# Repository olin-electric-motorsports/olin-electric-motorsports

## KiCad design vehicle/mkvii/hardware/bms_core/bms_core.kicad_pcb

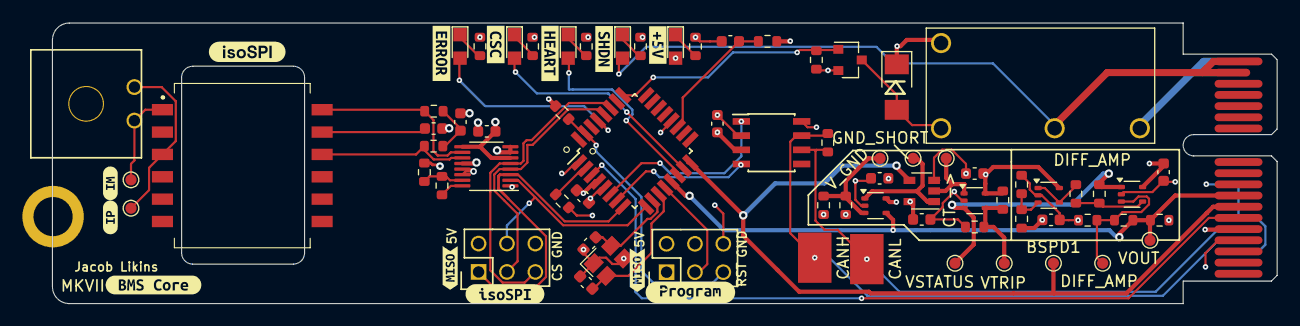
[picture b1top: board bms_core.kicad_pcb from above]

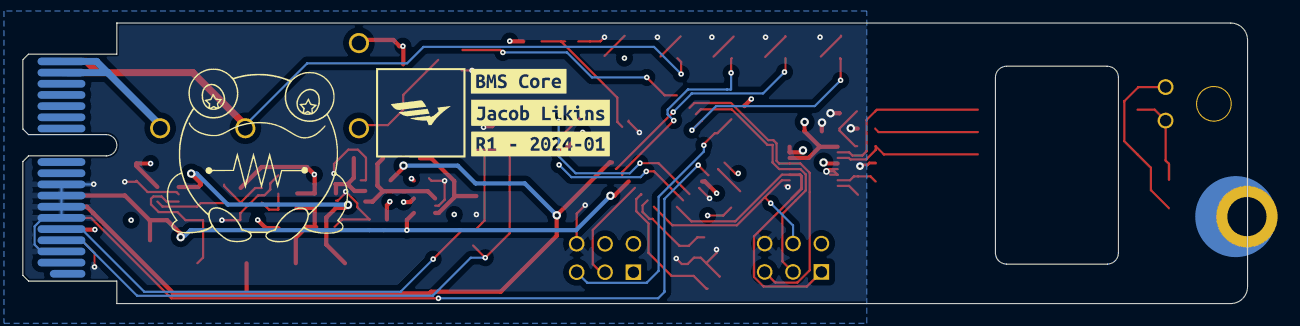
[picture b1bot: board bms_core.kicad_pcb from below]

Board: 4 copper layers, 109.6 x 25.1 mm, 89 parts (3 on the bottom side), 50 nets.

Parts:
BSPD1: BSPD_CURRENT_THRESH; TestPoint_Pad_D1.0mm
C1, C4, C6, C9, C10, C11, C12, C13: C_0.1uF; C_0603
C2: C_100pF; C_0603
C3, C5: C_30pF; C_0603
C7, C8: C_10nF; C_0603
CANH: CANH1; Test_Point_SMD
CANL: CANL1; Test_Point_SMD
CT ->: CURRENT_TRIP; TestPoint_Pad_D1.0mm
D1: LED_AMBER; CHIPLED_0805
D2: LED_GREEN; CHIPLED_0805
D3: LED_RED; CHIPLED_0805
D4: LED_WHITE; CHIPLED_0805
D5: D_Zener_18V_SMBJ5355B-TP; DO-214AA
D6: LED_BLUE; CHIPLED_0805
DIFF_AMP: TP_1mm; TestPoint_Pad_D1.0mm
GND_SHORT: GND_SHORT; TestPoint_Pad_D1.0mm
H2: CONN_MountingHole; PCIe_Mount
IM1: TP_1mm; TestPoint_Pad_D1.0mm
IP1: TP_1mm; TestPoint_Pad_D1.0mm
J1, J2: CONN_02x03; Pin_Header_Straight_2x03
J3: MicroFit_RA_2
J5: CONN_pcie_x1; pcie_x1
K1: Relay_G5Q-1A4-DC5; Relay_SPST_OMRON-G5Q-1A4_OEM
Q1: SSM3K333R; SOT-23F
R1, R3, R21, R22, R23: 1KR; R_0603
R2: R_100; R_0603
R4: 100R; R_0603
R5: R_120_DNP; R_0603
R6, R7, R12, R13, R14, R15, R16, R19, R24, R25: R_10K; R_0603
R8, R9, R18: R_1K; R_0603
R10, R11: R_60.4; R_0603
R17: R_1M; R_0603
R20: R_576; R_0603
T1: HM2112ZNLT
U1: ATMEGA64M1; TQFP-32_7x7mm_Pitch0.8mm
U2: MAX33011EASA; SOIC-8_3.9x4.9mm_Pitch1.27mm_OEM
U3: LTC6820HMS; MSOP-16_3x4mm_P0.5mm
U4, U5, U6, U8: MCP6001; SOT-353_SC-70-5
U7: SN74LVC1G32DBVR; SOT-23-5_OEM
VOUT: VOUT; TestPoint_Pad_D1.0mm
VSTATUS: VSTATUS; TestPoint_Pad_D1.0mm
VTRIP: VTRIP; TestPoint_Pad_D1.0mm
V_GND: V_GND_THRESHOLD; TestPoint_Pad_D1.0mm
Y1: Crystal_16MHz_18pF; Crystal_SMD_FA238
kibuzzard-63B930AD, kibuzzard-63B930AD#2: G***; kibuzzard-63B930AD
kibuzzard-63B9305B: G***; kibuzzard-63B9305B
kibuzzard-63B93076: G***; kibuzzard-63B93076
kibuzzard-63BB8A3F: G***; kibuzzard-63BB8A3F
kibuzzard-63BB8A53: G***; kibuzzard-63BB8A53
kibuzzard-63BF4A21: G***; kibuzzard-63BF4A21
kibuzzard-63BF57C4: G***; kibuzzard-63BF57C4
kibuzzard-673AE5B2: G***; kibuzzard-673AE5B2
kibuzzard-673AE5D1: G***; kibuzzard-673AE5D1
kibuzzard-673AE69E: G***; kibuzzard-673AE69E
kibuzzard-673AE93C: G***; kibuzzard-673AE93C
kibuzzard-673AE677: G***; kibuzzard-673AE677
kibuzzard-673AE688: G***; kibuzzard-673AE688
kibuzzard-673AE955: G***; kibuzzard-673AE955
kibuzzard-673AE966: G***; kibuzzard-673AE966

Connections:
+5V: C1.1, C4.1, C6.1, C9.1, C10.1, C11.1, C12.1, C13.1, D4.2 (A), D5.1 (K), J1.2, J2.2, J5.B5 (5V), K1.5, R2.1, R6.1, R12.2, R17.1, R19.2, R24.1, U1.4 (VCC), U2.3 (VDD), U3.6 (VDDS), U3.7 (POL), U3.8 (PHA), U3.9 (VDD), U3.12 (MSTR), U4.5 (V+), U5.5 (V+), U6.5 (V+), U7.5 (VCC), U8.5 (V+)
/BMS_RELAY_DRIVE: Q1.1 (G), R7.2, U1.25 ((PCINT15/D2A/AMP2+)PC7)
/BSPD Current Sensor Trigger/CURRENT_TRIP: CT ->.1, U6.1, U7.2 (in)
/BSPD Current Sensor Trigger/GND_SHORT: GND_SHORT.1, U5.1, U7.1 (in)
/BSPD Current Sensor Trigger/VSTATUS: R15.2, U4.1, U6.3 (+), VSTATUS.1
/BSPD Current Sensor Trigger/VTRIP: R19.1, R20.1, U6.4 (-), VTRIP.1
/BSPD Current Sensor Trigger/V_GND_THRESHOLD: R17.2, R18.1, U5.3 (+), V_GND.1
/BSPD_CURRENT_THRESH: BSPD1.1, J5.B7 (io_3), U1.16 ((PCINT2/ADC5/INT1/ACMPN0)PB2), U7.4 (out)
/CANH: CANH.1, J5.A4 (CAN+), R5.1, U2.7 (CANH)
/CANL: CANL.1, J5.A5 (CAN-), R5.2, U2.6 (CANL)
/CSC_Comms: D2.2 (A), U1.15 ((PCINT23/ACMP0)PD7)
/Error: D3.2 (A), U1.29 ((PCINT16/PSCOUT0A)PD0)
/FAN_PWM: J5.B6 (io_1), U1.3 ((PCINT9/PSCIN1/OC1B/~SS_A)PC1)
/Heartbeat: D1.2 (A), U1.14 ((PCINT22/ADC3/INT0/ACMPN2)PD6)
/IM: IM1.1, J3.1, T1.1
/IP: IP1.1, J3.2, T1.3
/ISO_CS: J2.5, U1.27 ((PCINT6/ADC7/PSCOUT1B)PB6), U3.5 (~CS)
/ISO_MISO: J2.1, U1.8 ((PCINT0/MISO/PSCOUT2A)PB0), U3.3 (MISO)
/ISO_MOSI: J2.4, U1.9 ((PCINT1/MOSI/PSCOUT2B)PB1), U3.2 (MOSI)
/ISO_SCK: J2.3, U1.28 ((PCINT7/ADC4/SCK/PSCOUT0B)PB7), U3.4 (SCK)
/MISO: J1.1, U1.1 ((PCINT18/PSCIN2/OC1A/MISO_A)PD2)
/MOSI: J1.4, R4.1
/RESET: J1.5, R6.2, U1.31 ((PCINT24/OCD/~RESET)PE0)
/RXCAN: U1.7 ((PCINT11/T1/ICP1B/RXCAN)PC3), U2.4 (RXD)
/SCK: J1.3, U1.12 ((PCINT20/ADC1/RXD/RXLIN/ICP1A/SCK_A)PD4)
/SHDN_IN: J5.A17 (SHDN_IN/io_22), J5.A18 (SHDN_IN/io_24), K1.3
/SHDN_OUT: D6.2 (A), J5.B17 (SHDN_OUT/io_23), J5.B18 (SHDN_OUT/io_25), K1.2
/TXCAN: U1.6 ((PCINT10/T0/TXCAN)PC2), U2.1 (TXD)
/VOUT_CURRENT_SENSE: J5.B8 (io_5), R12.1, R13.1, U1.13 ((PCINT21/ADC2/ACMP2)PD5), U5.4 (-), VOUT.1
GND: C1.2, C2.2, C3.2, C4.2, C5.2, C6.2, C7.2, C8.2, C9.2, C10.2, C11.2, C12.2, C13.2, J1.6, J2.6, J5.A3 (GND), J5.A6 (io_0), J5.A7 (io_2), J5.A8 (io_4), J5.A9 (io_6), J5.B4 (GND), Q1.2 (S), R1.2, R3.2, R7.1, R9.2, R14.1, R18.2, R20.2, R21.2, R22.2, R23.2, R25.2, U1.5 (GND), U1.20 (AGND), U2.2 (VSS), U2.8 (STBY), U3.1 (EN), U3.13 (SLOW), U3.14 (GND), U4.2 (V-), U5.2 (V-), U6.2 (V-), U7.3 (GND), U8.2 (V-), Y1.2, Y1.4
unnamed: C7.1, R10.2, R11.1
unnamed: C8.1, T1.11
unnamed: D1.1 (K), R1.1
unnamed: D2.1 (K), R3.1
unnamed: D3.1 (K), R21.1
unnamed: D4.1 (K), R22.1
unnamed: D5.2 (A), K1.1, Q1.3 (D)
unnamed: D6.1 (K), R23.1
unnamed: R4.2, U1.2 ((PCINT19/TXD/TXLIN/OC0A/~SS/MOSI_A)PD3)
unnamed: C5.1, U1.10 ((PCINT25/OC0B/XTAL1)PE1), Y1.3
unnamed: C3.1, U1.11 ((PCINT26/ADC0/XTAL2)PE2), Y1.1
unnamed: C2.1, R2.2, U1.19 (AVCC)
unnamed: R8.1, U3.16 (IBIAS)
unnamed: R8.2, R9.1, U3.15 (ICMP)
unnamed: R10.1, T1.12, U3.10 (IM)
unnamed: R11.2, T1.10, U3.11 (IP)
unnamed: DIFF_AMP.1, R13.2, R14.2, U4.3 (+)
unnamed: R15.1, R16.2, U4.4 (-)
unnamed: R24.2, R25.1, U8.3 (+)
unnamed: R16.1, U8.1, U8.4 (-)

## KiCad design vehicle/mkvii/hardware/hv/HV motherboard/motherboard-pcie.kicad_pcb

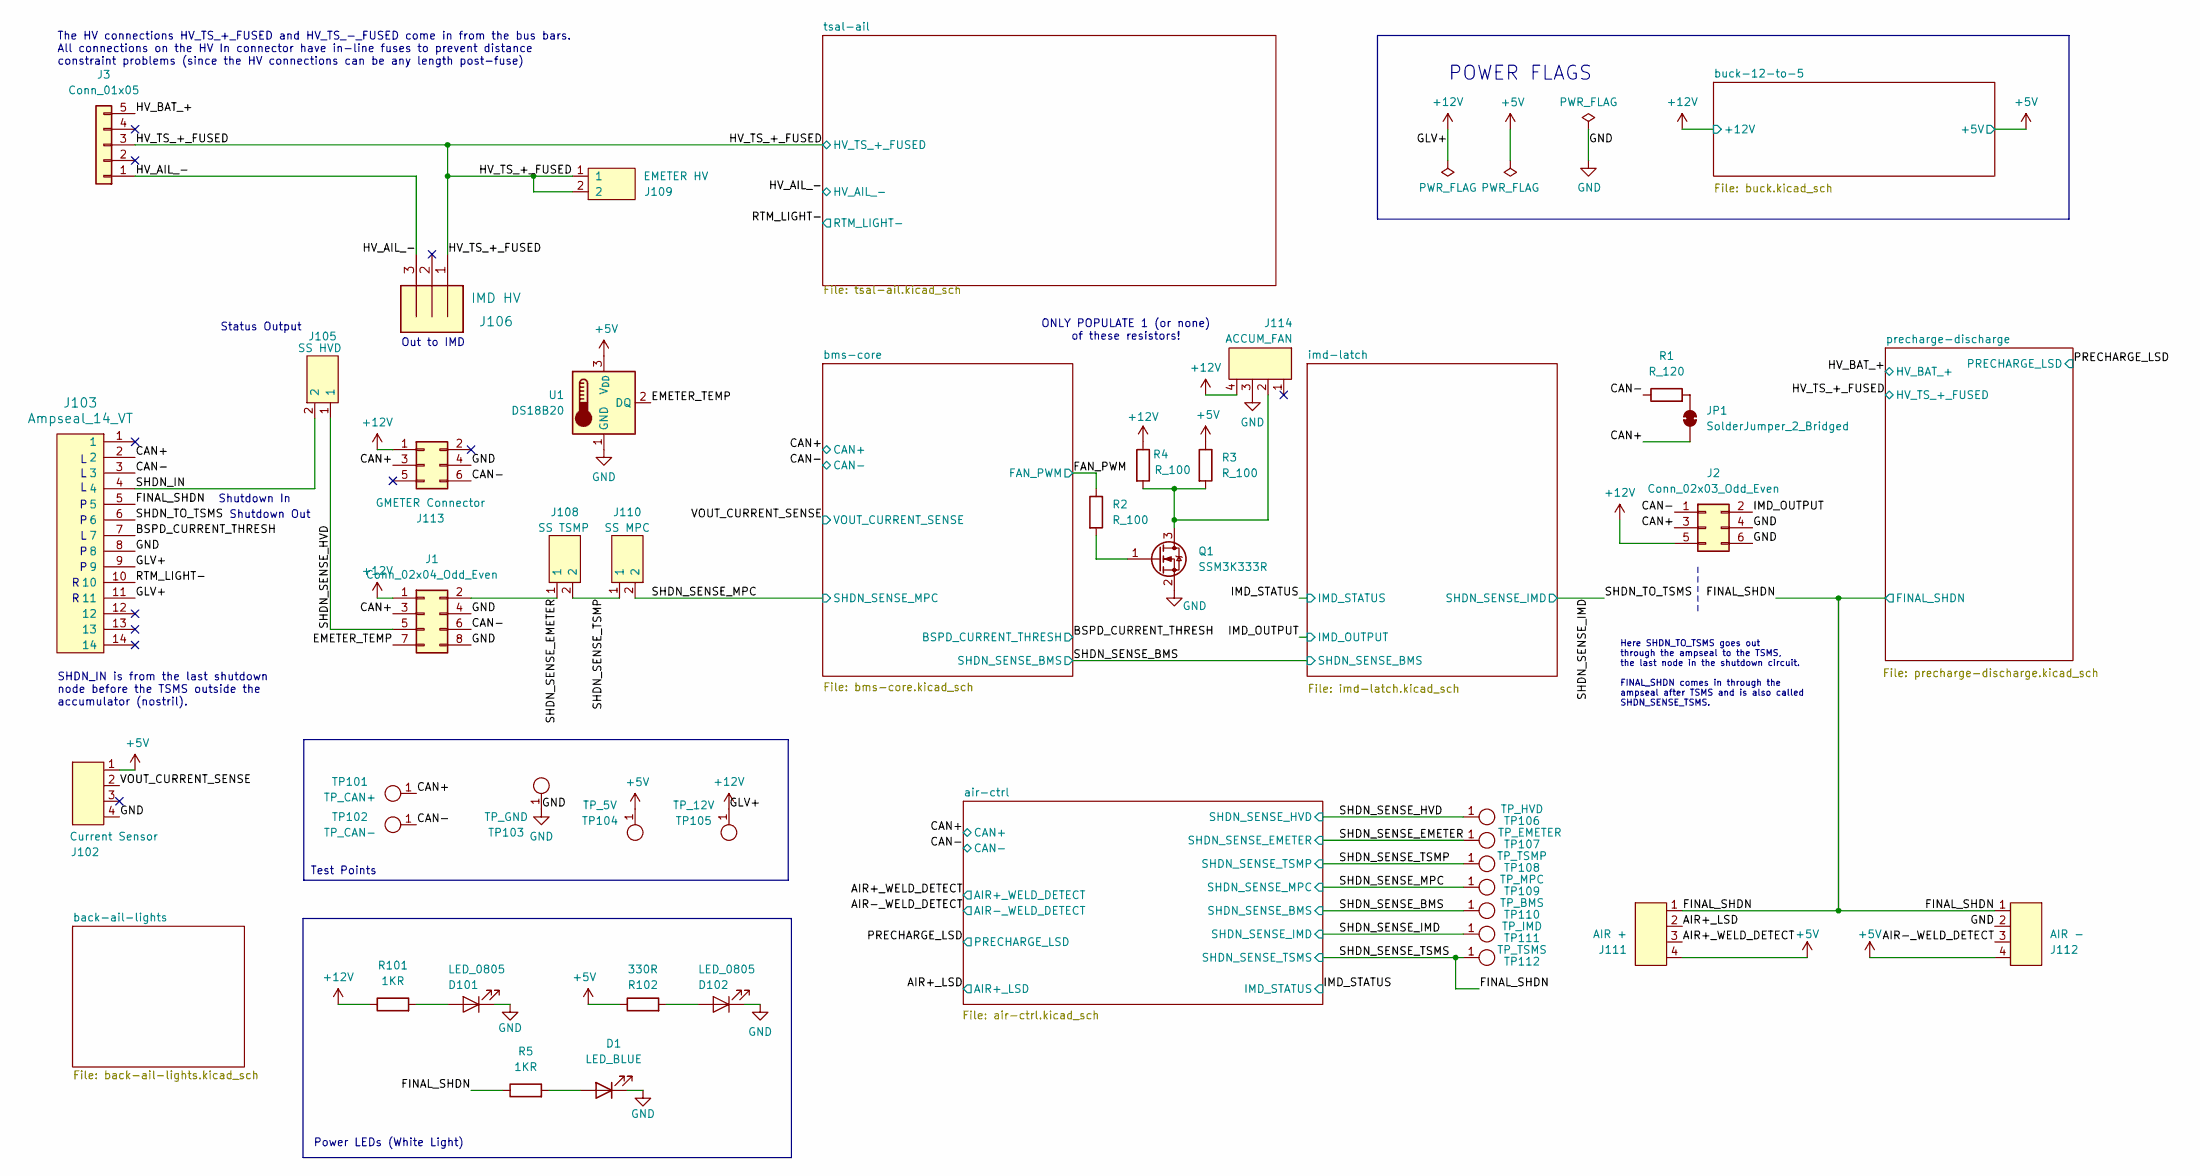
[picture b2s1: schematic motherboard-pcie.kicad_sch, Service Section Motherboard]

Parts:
D1: LED_BLUE; CHIPLED_0805; MPN LTST-C171TBKT
D101, D102: LED_0805; LED_0805_OEM; MPN 475-1410-1-ND
J1: Conn_02x04_Odd_Even; Molex_Micro-Fit_3.0_43045-0812_2x04_P3.00mm_Vertical
J2: Conn_02x03_Odd_Even; Molex_Micro-Fit_3.0_43045-0612_2x03_P3.00mm_Vertical
J3: Conn_01x05; Molex_Micro-Fit_3.0_43650-0515_1x05_P3.00mm_Vertical
J102: Current Sensor; MicroFit_VT_4; MPN 430450414
J103: Ampseal_14_VT; Ampseal_14; MPN 1-776261-1
J105: SS HVD; MicroFit_V_2; MPN WM10660-ND
J106: IMD HV; MicroFit_VT_3; MPN 436500327
J108: SS TSMP; MicroFit_V_2; MPN WM10660-ND
J109: EMETER HV; MicroFit_V_2; MPN WM10660-ND
J110: SS MPC; MicroFit_V_2; MPN WM10660-ND
J111: AIR +; MicroFit_VT_4; MPN 430450414
J112: AIR -; MicroFit_VT_4; MPN 430450414
J113: GMETER Connector; Molex_Micro-Fit_3.0_43045-0612_2x03_P3.00mm_Vertical
J114: ACCUM_FAN; MicroFit_VT_4; MPN 430450414
JP1: SolderJumper_2_Bridged; SolderJumper-2_P1.3mm_Bridged2Bar_Pad1.0x1.5mm
Q1: SSM3K333R; SOT-23F; MPN SSM3K333R,LF
R1: R_120; R_0603; MPN RC0603FR-13120RL
R2, R3, R4: R_100; R_0603; MPN RMCF0603FT1K00
R5, R101: 1KR; R_0603; MPN RMCF0603FT1K00
R102: 330R; R_0603; MPN WR06X3300FTL
TP101: TP_CAN+; Test_Point_SMD; MPN 5019
TP102: TP_CAN-; Test_Point_SMD; MPN 5019
TP103: TP_GND; Test_Point_SMD; MPN 5019
TP104: TP_5V; Test_Point_SMD; MPN 5019
TP105: TP_12V; Test_Point_SMD; MPN 5019
TP106: TP_HVD; Test_Point_SMD; MPN 5019
TP107: TP_EMETER; Test_Point_SMD; MPN 5019
TP108: TP_TSMP; Test_Point_SMD; MPN 5019
TP109: TP_MPC; Test_Point_SMD; MPN 5019
TP110: TP_BMS; Test_Point_SMD; MPN 5019
TP111: TP_IMD; Test_Point_SMD; MPN 5019
TP112: TP_TSMS; Test_Point_SMD; MPN 5019
U1: DS18B20; TO-92_Inline

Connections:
+5V: J102.1, J111.4, J112.4, R3.1, R102.1, TP104.1, U1.3 (V_{DD}); also elsewhere on the board
+12V: J1.1, J2.5, J103.9, J103.11, J113.1, J114.4, R4.1, R101.1, TP105.1; also elsewhere on the board
/AIR+_LSD: J111.2; also elsewhere on the board
/AIR+_WELD_DETECT: J111.3; also elsewhere on the board
/AIR-_WELD_DETECT: J112.3; also elsewhere on the board
/BSPD_CURRENT_THRESH: J103.7; also elsewhere on the board
/CAN+: J1.3, J2.3, J103.2, J113.3, JP1.1 (A), TP101.1; also elsewhere on the board
/CAN-: J1.6, J2.1, J103.3, J113.6, R1.1, TP102.1; also elsewhere on the board
/EMETER_TEMP: J1.7, U1.2 (DQ)
/FAN_PWM: R2.1; also elsewhere on the board
/FINAL_SHDN: J103.5, J111.1, J112.1, R5.1, TP112.1; also elsewhere on the board
/HV_AIL_-: J3.1, J106.3; also elsewhere on the board
/HV_BAT_+: J3.5; also elsewhere on the board
/HV_TS_+_FUSED: J3.3, J106.1, J109.1, J109.2; also elsewhere on the board
/IMD_OUTPUT: J2.2; also elsewhere on the board
/RTM_LIGHT-: J103.10; also elsewhere on the board
/SHDN_IN: J103.4, J105.2
/SHDN_SENSE_BMS: TP110.1; also elsewhere on the board
/SHDN_SENSE_EMETER: J1.2, J108.1, TP107.1; also elsewhere on the board
/SHDN_SENSE_HVD: J1.5, J105.1, TP106.1; also elsewhere on the board
/SHDN_SENSE_IMD: J103.6, TP111.1; also elsewhere on the board
/SHDN_SENSE_MPC: J110.2, TP109.1; also elsewhere on the board
/SHDN_SENSE_TSMP: J108.2, J110.1, TP108.1; also elsewhere on the board
/VOUT_CURRENT_SENSE: J102.2; also elsewhere on the board
GND: D1.1 (K), D101.1 (K), D102.1 (K), J1.4, J1.8, J2.4, J2.6, J102.4, J103.8, J112.2, J113.4, J114.3, Q1.2 (S), TP103.1, U1.1 (GND); also elsewhere on the board
unnamed: D1.2 (A), R5.2
unnamed: D101.2 (A), R101.2
unnamed: D102.2 (A), R102.2
unnamed: JP1.2 (B), R1.2
unnamed: J114.2, Q1.3 (D), R3.2, R4.2
unnamed: Q1.1 (G), R2.2

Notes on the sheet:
SHDN_IN is from the last shutdown node before the TSMS outside the accumulator (nostril).
Shutdown Out
Test Points
Shutdown In
Here SHDN_TO_TSMS goes out through the ampseal to the TSMS, the last node in the shutdown circuit. FINAL_SHDN comes in through the ampseal after TSMS and is also called SHDN_SENSE_TSMS.
Power LEDs (White Light)
POWER FLAGS
Status Output
ONLY POPULATE 1 (or none) of these resistors!
Out to IMD
The HV connections HV_TS_+_FUSED and HV_TS_-_FUSED come in from the bus bars. All connections on the HV In connector have in-line fuses to prevent distance constraint problems (since the HV connections can be any length post-fuse)

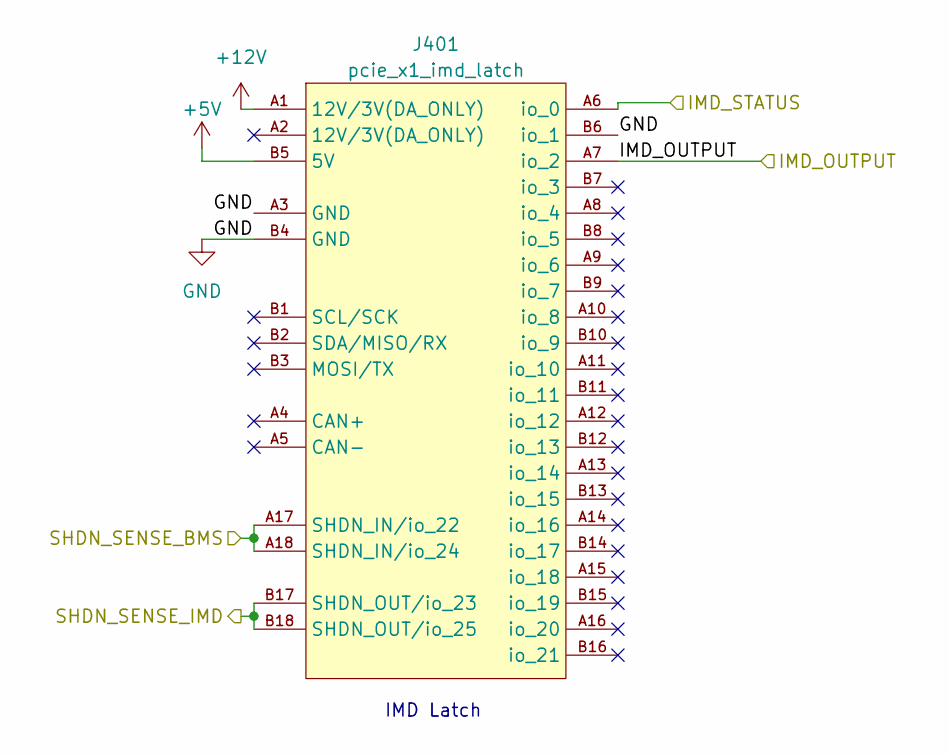
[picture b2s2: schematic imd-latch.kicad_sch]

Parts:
J401: pcie_x1_imd_latch; te_pcie_x1_connector

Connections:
+5V: J401.B5 (5V); also elsewhere on the board
+12V: J401.A1 (12V/3V(DA_ONLY)); also elsewhere on the board
/IMD_OUTPUT: J401.A7 (io_2); also elsewhere on the board
/IMD_STATUS: J401.A6 (io_0); also elsewhere on the board
/SHDN_SENSE_BMS: J401.A17 (SHDN_IN/io_22), J401.A18 (SHDN_IN/io_24); also elsewhere on the board
/SHDN_SENSE_IMD: J401.B17 (SHDN_OUT/io_23), J401.B18 (SHDN_OUT/io_25); also elsewhere on the board
GND: J401.A3 (GND), J401.B4 (GND), J401.B6 (io_1); also elsewhere on the board

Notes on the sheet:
IMD Latch

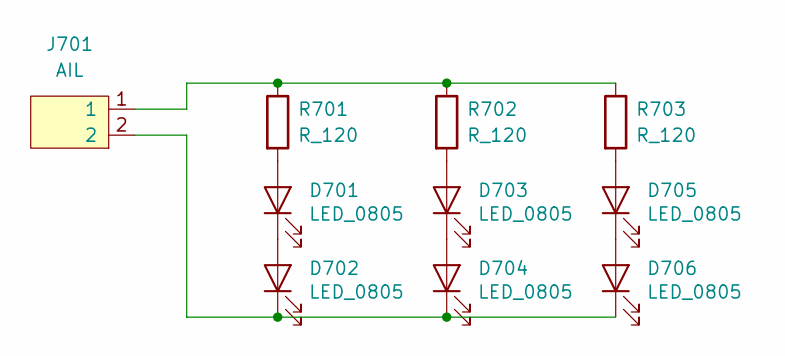
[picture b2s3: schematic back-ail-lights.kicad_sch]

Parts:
D701, D702, D703, D704, D705, D706: LED_0805; LED_0805_OEM_no_border; MPN 475-1410-1-ND
J701: AIL; MicroFit_V_2; MPN WM10660-ND
R701, R702, R703: R_120; R_0805_OEM; MPN 667-ERJ-6ENF1200V

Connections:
unnamed: D701.2 (A), R701.2
unnamed: D701.1 (K), D702.2 (A)
unnamed: D702.1 (K), D704.1 (K), D706.1 (K), J701.2
unnamed: D703.2 (A), R702.2
unnamed: D703.1 (K), D704.2 (A)
unnamed: D705.2 (A), R703.2
unnamed: D705.1 (K), D706.2 (A)
unnamed: J701.1, R701.1, R702.1, R703.1

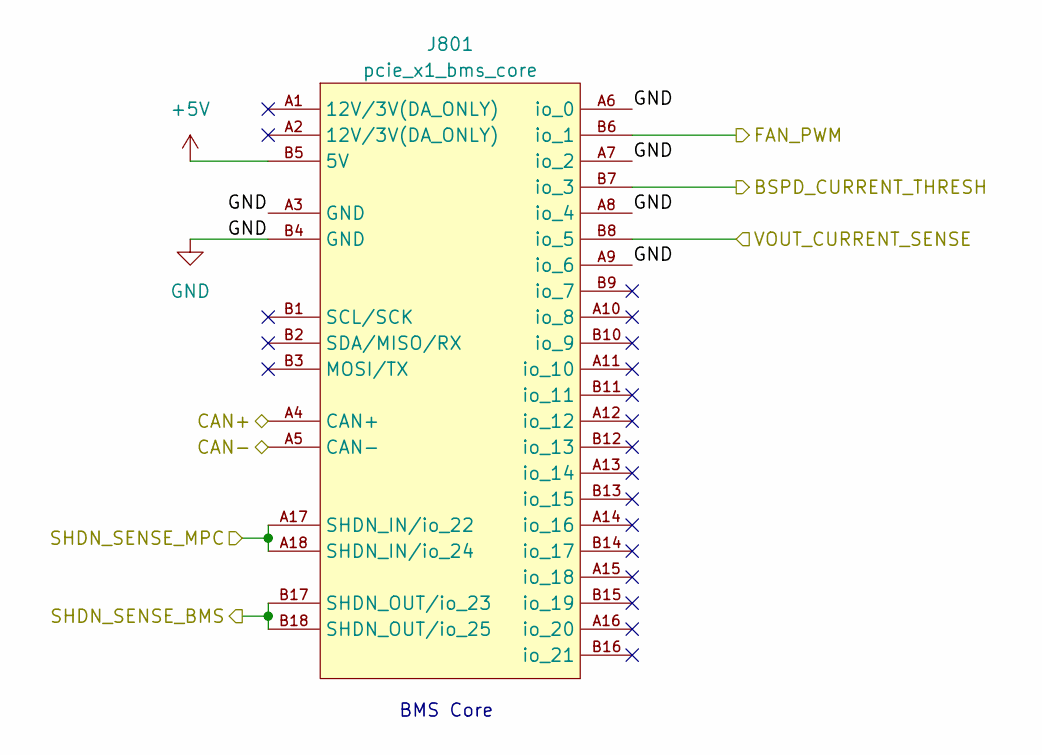
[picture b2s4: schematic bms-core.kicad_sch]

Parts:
J801: pcie_x1_bms_core; te_pcie_x1_connector

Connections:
+5V: J801.B5 (5V); also elsewhere on the board
/BSPD_CURRENT_THRESH: J801.B7 (io_3); also elsewhere on the board
/CAN+: J801.A4 (CAN+); also elsewhere on the board
/CAN-: J801.A5 (CAN-); also elsewhere on the board
/FAN_PWM: J801.B6 (io_1); also elsewhere on the board
/SHDN_SENSE_BMS: J801.B17 (SHDN_OUT/io_23), J801.B18 (SHDN_OUT/io_25); also elsewhere on the board
/SHDN_SENSE_MPC: J801.A17 (SHDN_IN/io_22), J801.A18 (SHDN_IN/io_24); also elsewhere on the board
/VOUT_CURRENT_SENSE: J801.B8 (io_5); also elsewhere on the board
GND: J801.A3 (GND), J801.A6 (io_0), J801.A7 (io_2), J801.A8 (io_4), J801.A9 (io_6), J801.B4 (GND); also elsewhere on the board

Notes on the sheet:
BMS Core

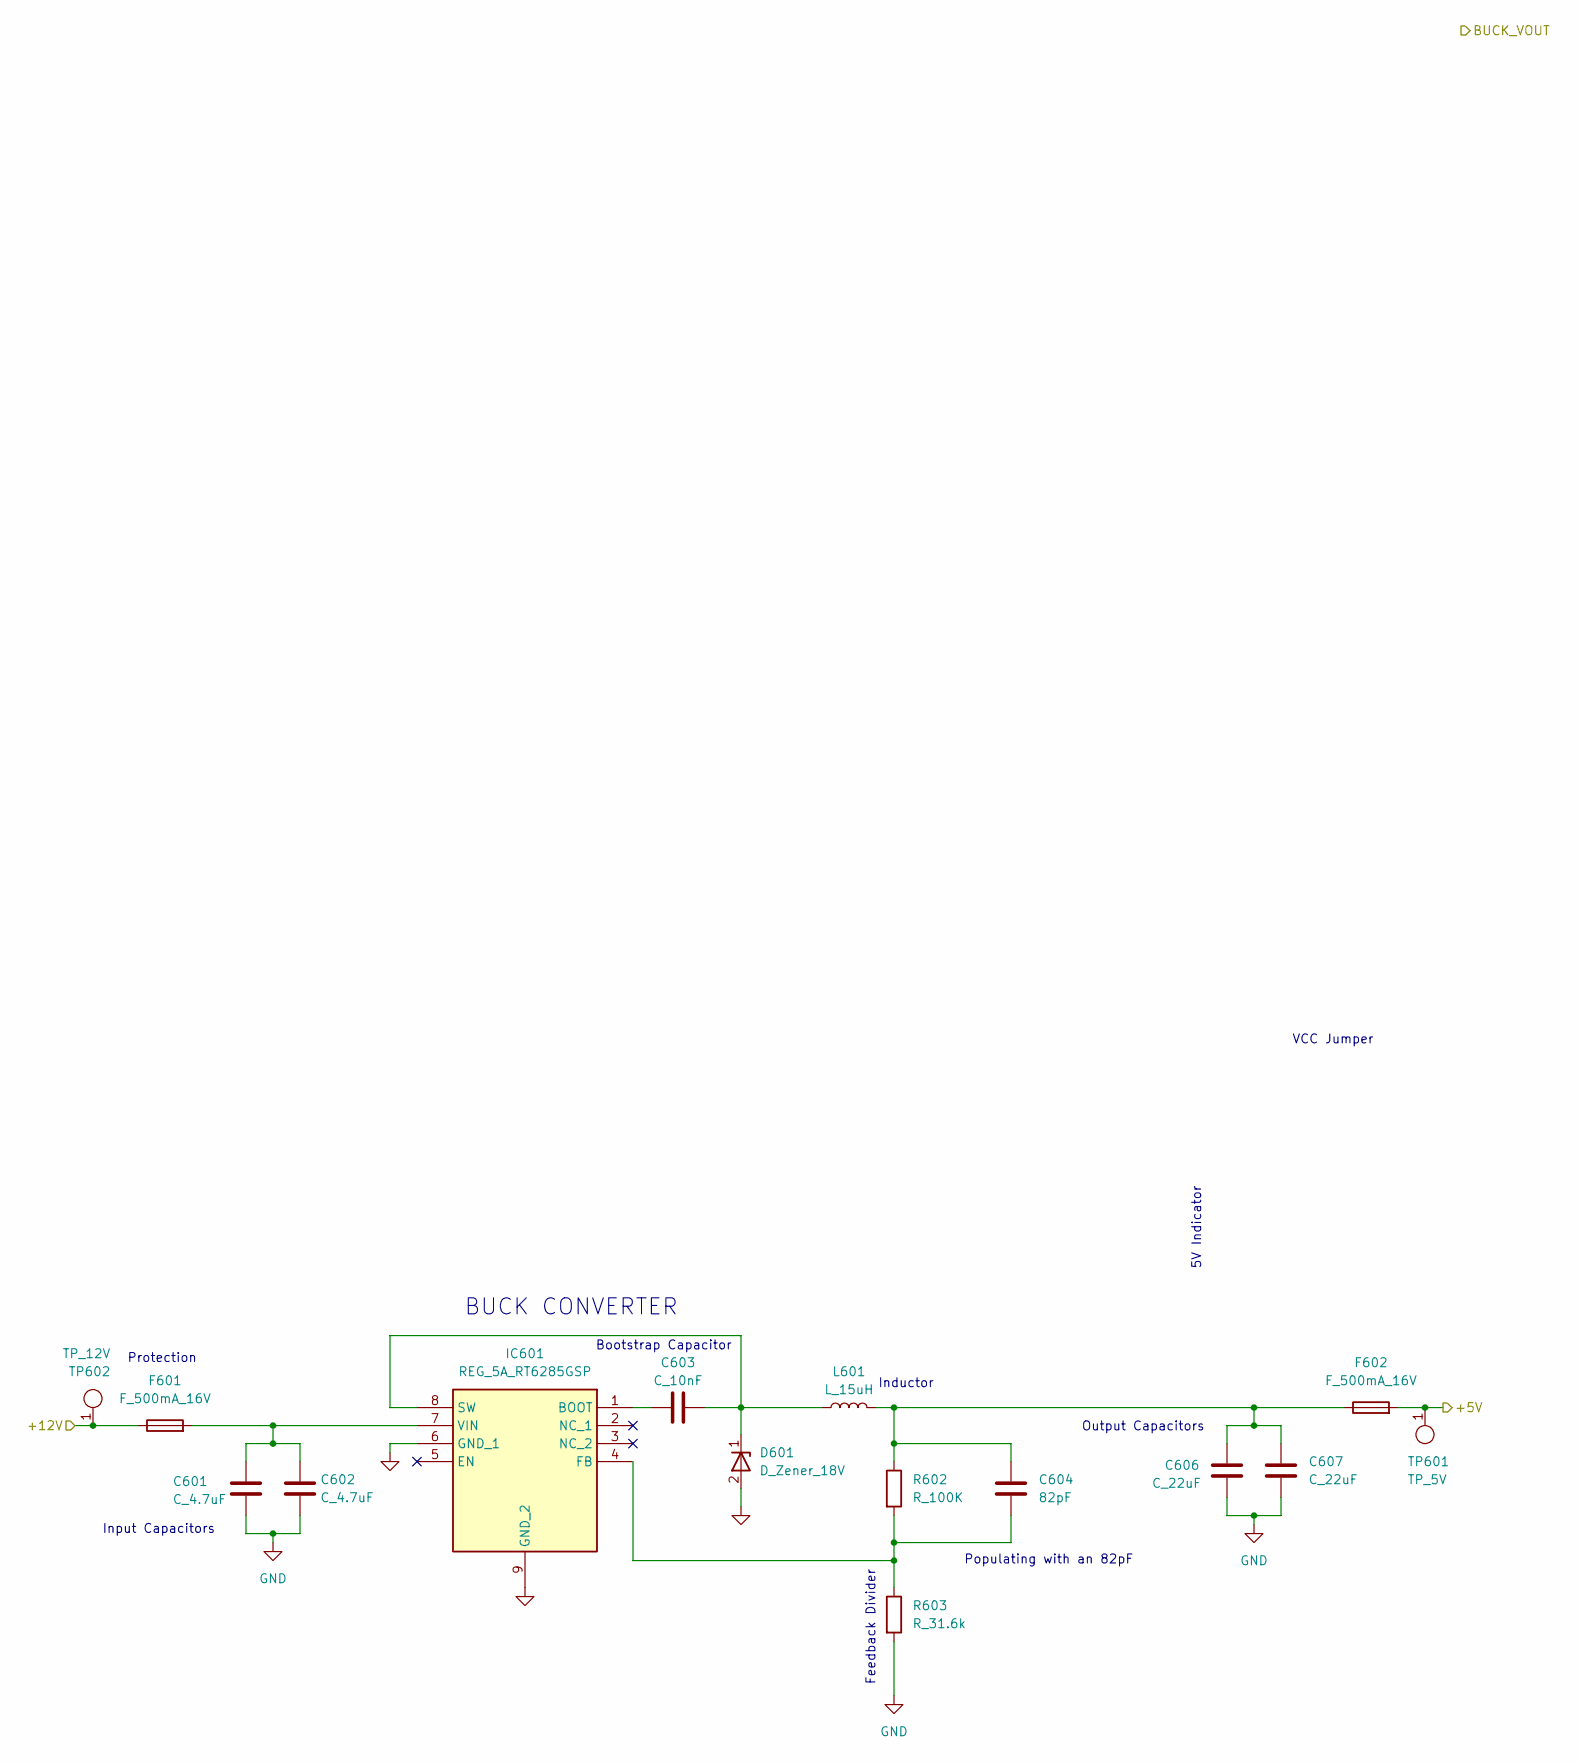
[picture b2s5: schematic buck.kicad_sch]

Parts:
C601, C602: C_4.7uF; C_0603; MPN GRT188R61E475ME13D
C603: C_10nF; C_0603; MPN CL10B103KB8NNNC
C604: 82pF; C_0603; MPN 0603N101F101CT
C606, C607: C_22uF; C_1206_3216Metric; MPN CL31A226KAHNNNE
D601: D_Zener_18V; DO-214AA; MPN SMBJ5355B-TP
F601, F602: F_500mA_16V; Fuse_1210; MPN 0ZCH0050FF2G
IC601: REG_5A_RT6285GSP; SOIC127P600X175-9N; Mouser Part Number 835-RT6285GSP
L601: L_15uH; NR10050T150M; MPN NR10050T150M
R602: R_100K; R_0603; MPN RMCF0603FT100K
R603: R_31.6k; R_0603; MPN RMCF0603FT75K0
TP601: TP_5V; TestPoint_Pad_D1.0mm
TP602: TP_12V; TestPoint_Pad_D1.0mm

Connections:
+5V: F602.2, TP601.1; also elsewhere on the board
+12V: F601.1, TP602.1; also elsewhere on the board
GND: C601.2, C602.2, C606.2, C607.2, D601.2 (A), IC601.6 (GND_1), IC601.9 (GND_2), R603.2; also elsewhere on the board
unnamed: C604.1, C606.1, C607.1, F602.1, L601.2, R602.1
unnamed: C603.2, D601.1 (K), IC601.8 (SW), L601.1
unnamed: C603.1, IC601.1 (BOOT)
unnamed: C604.2, IC601.4 (FB), R602.2, R603.1
unnamed: C601.1, C602.1, F601.2, IC601.7 (VIN)

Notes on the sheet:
Inductor
Bootstrap Capacitor
Populating with an 82pF
5V Indicator
Output Capacitors
Protection
VCC Jumper
BUCK CONVERTER
Feedback Divider
Input Capacitors

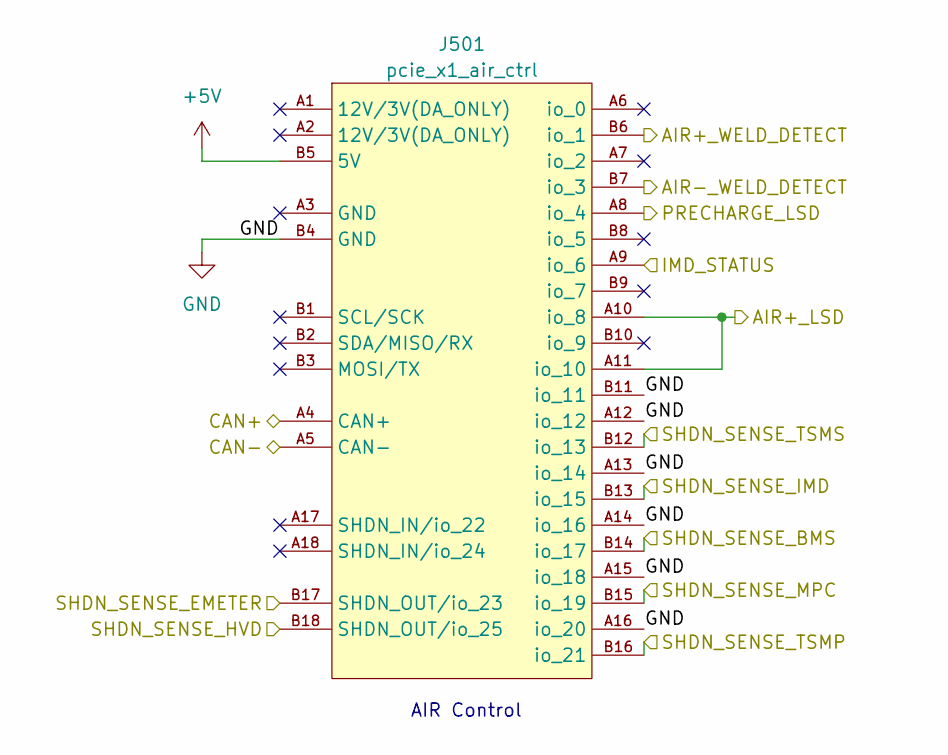
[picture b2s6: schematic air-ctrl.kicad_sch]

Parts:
J501: pcie_x1_air_ctrl; te_pcie_x1_connector

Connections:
+5V: J501.B5 (5V); also elsewhere on the board
/AIR+_LSD: J501.A10 (io_8), J501.A11 (io_10); also elsewhere on the board
/AIR+_WELD_DETECT: J501.B6 (io_1); also elsewhere on the board
/AIR-_WELD_DETECT: J501.B7 (io_3); also elsewhere on the board
/CAN+: J501.A4 (CAN+); also elsewhere on the board
/CAN-: J501.A5 (CAN-); also elsewhere on the board
/FINAL_SHDN: J501.B12 (io_13); also elsewhere on the board
/IMD_STATUS: J501.A9 (io_6); also elsewhere on the board
/PRECHARGE_LSD: J501.A8 (io_4); also elsewhere on the board
/SHDN_SENSE_BMS: J501.B14 (io_17); also elsewhere on the board
/SHDN_SENSE_EMETER: J501.B17 (SHDN_OUT/io_23); also elsewhere on the board
/SHDN_SENSE_HVD: J501.B18 (SHDN_OUT/io_25); also elsewhere on the board
/SHDN_SENSE_IMD: J501.B13 (io_15); also elsewhere on the board
/SHDN_SENSE_MPC: J501.B15 (io_19); also elsewhere on the board
/SHDN_SENSE_TSMP: J501.B16 (io_21); also elsewhere on the board
GND: J501.A12 (io_12), J501.A13 (io_14), J501.A14 (io_16), J501.A15 (io_18), J501.A16 (io_20), J501.B4 (GND), J501.B11 (io_11); also elsewhere on the board

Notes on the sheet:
AIR Control

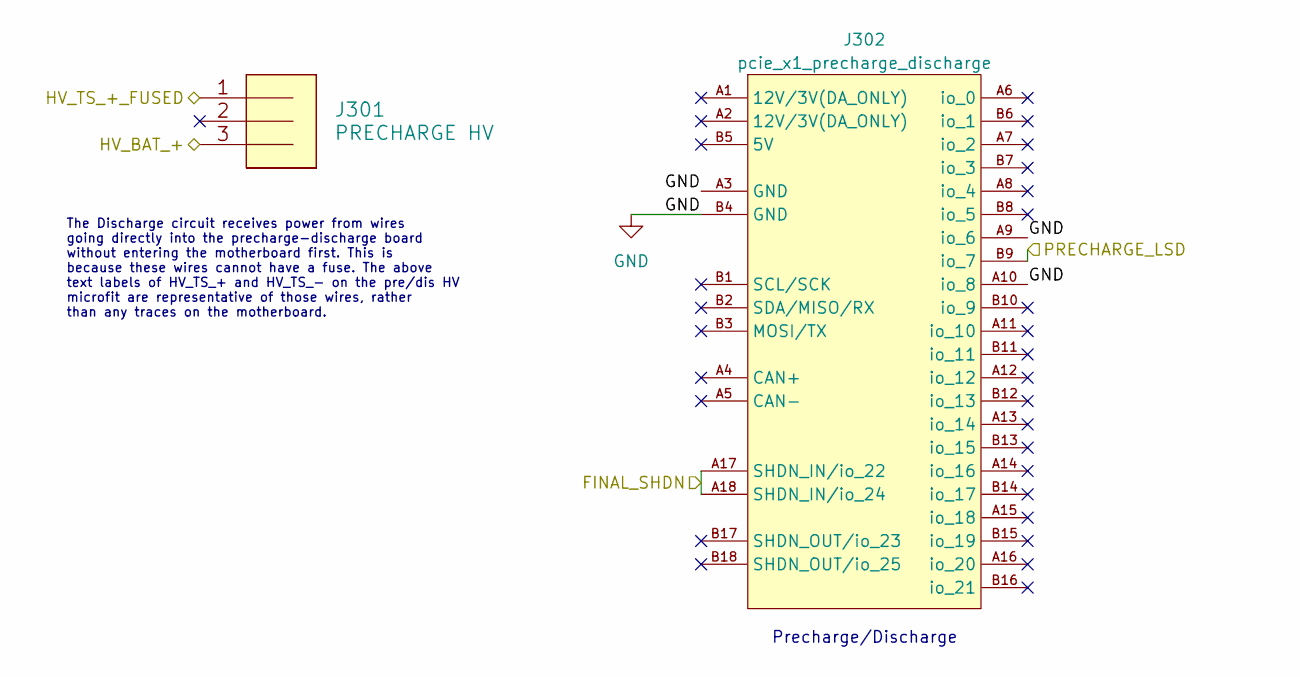
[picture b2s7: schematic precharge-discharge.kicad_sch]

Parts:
J301: PRECHARGE HV; MicroFit_VT_3; MPN 436500327
J302: pcie_x1_precharge_discharge; te_pcie_x1_connector

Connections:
/FINAL_SHDN: J302.A17 (SHDN_IN/io_22), J302.A18 (SHDN_IN/io_24); also elsewhere on the board
/HV_BAT_+: J301.3; also elsewhere on the board
/HV_TS_+_FUSED: J301.1; also elsewhere on the board
/PRECHARGE_LSD: J302.B9 (io_7); also elsewhere on the board
GND: J302.A3 (GND), J302.A9 (io_6), J302.A10 (io_8), J302.B4 (GND); also elsewhere on the board

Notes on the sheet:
Precharge/Discharge
The Discharge circuit receives power from wires going directly into the precharge-discharge board without entering the motherboard first. This is because these wires cannot have a fuse. The above text labels of HV_TS_+ and HV_TS_- on the pre/dis HV microfit are representative of those wires, rather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

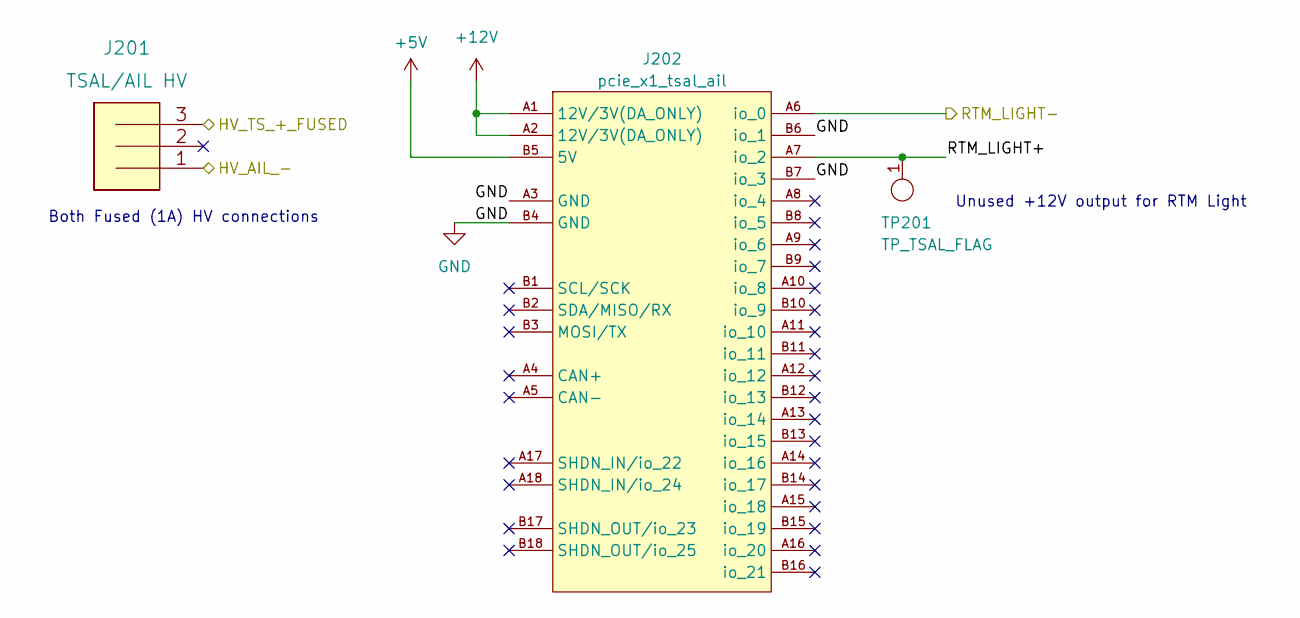
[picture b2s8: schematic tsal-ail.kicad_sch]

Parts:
J201: TSAL/AIL HV; MicroFit_VT_3; MPN 436500327
J202: pcie_x1_tsal_ail; te_pcie_x1_connector
TP201: TP_TSAL_FLAG; TestPoint_Pad_D1.0mm

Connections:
+5V: J202.B5 (5V); also elsewhere on the board
+12V: J202.A1 (12V/3V(DA_ONLY)), J202.A2 (12V/3V(DA_ONLY)); also elsewhere on the board
/HV_AIL_-: J201.1; also elsewhere on the board
/HV_TS_+_FUSED: J201.3; also elsewhere on the board
/RTM_LIGHT-: J202.A6 (io_0); also elsewhere on the board
/tsal-ail/RTM_LIGHT+: J202.A7 (io_2), TP201.1
GND: J202.A3 (GND), J202.B4 (GND), J202.B6 (io_1), J202.B7 (io_3); also elsewhere on the board

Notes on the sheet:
Both Fused (1A) HV connections
Unused +12V output for RTM Light

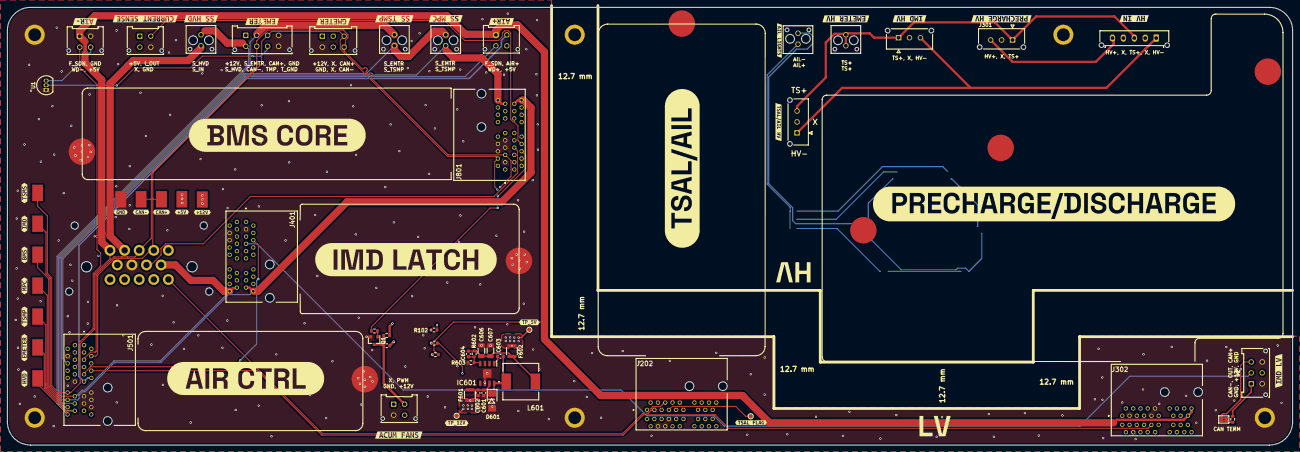
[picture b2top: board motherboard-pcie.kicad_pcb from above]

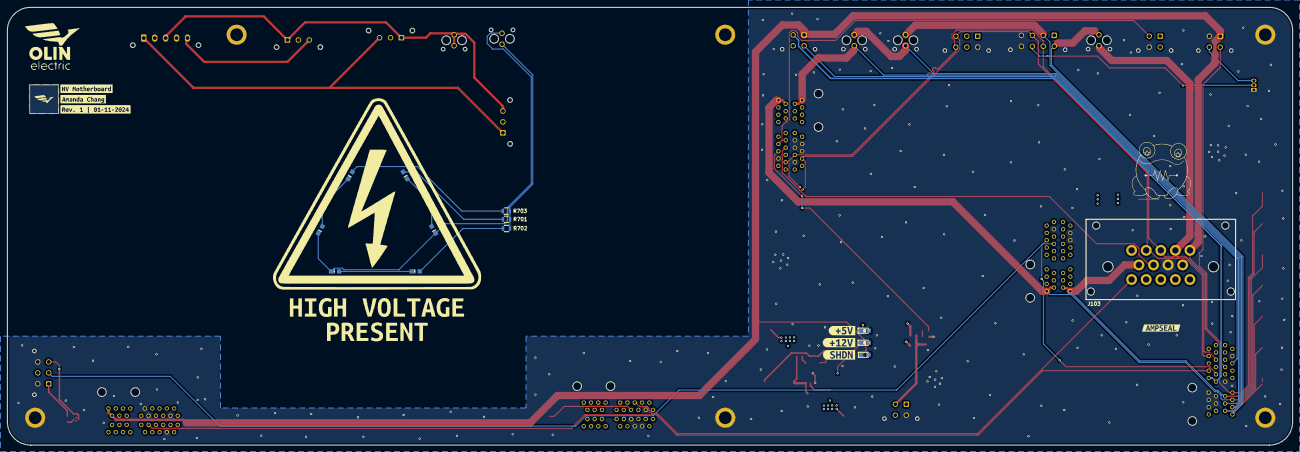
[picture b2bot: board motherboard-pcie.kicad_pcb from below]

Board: 4 copper layers, 352.4 x 120.0 mm, 119 parts (22 on the bottom side), 47 nets.

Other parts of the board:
kibuzzard-640B75B2: G***; kibuzzard-640B75B2
kibuzzard-640B76B0: G***; kibuzzard-640B76B0
kibuzzard-640B87CD: G***; kibuzzard-640B87CD
kibuzzard-640B861F: G***; kibuzzard-640B861F
kibuzzard-640B8645: G***; kibuzzard-640B8645
kibuzzard-640B8668: G***; kibuzzard-640B8668
kibuzzard-640B8680: G***; kibuzzard-640B8680
kibuzzard-677B3C3E: G***; kibuzzard-677B3C3E
kibuzzard-677B3C38: G***; kibuzzard-677B3C38
kibuzzard-677B3E90: G***; kibuzzard-677B3E90
kibuzzard-677CE749: G***; kibuzzard-677CE749
kibuzzard-677CFB84: G***; kibuzzard-677CFB84
kibuzzard-677CFB97: G***; kibuzzard-677CFB97
kibuzzard-677CFBA0: G***; kibuzzard-677CFBA0
kibuzzard-677E2BD4: G***; kibuzzard-677E2BD4
kibuzzard-677E2BDC: G***; kibuzzard-677E2BDC
kibuzzard-677E2BE2: G***; kibuzzard-677E2BE2
kibuzzard-677E2BE7: G***; kibuzzard-677E2BE7
kibuzzard-677E2BEC: G***; kibuzzard-677E2BEC
kibuzzard-677E2BF5: G***; kibuzzard-677E2BF5
kibuzzard-677E2BFE: G***; kibuzzard-677E2BFE
kibuzzard-677E26A9: G***; kibuzzard-677E26A9
kibuzzard-677E26B0: G***; kibuzzard-677E26B0
kibuzzard-677E26B5: G***; kibuzzard-677E26B5
kibuzzard-677E26BE: G***; kibuzzard-677E26BE
kibuzzard-677E26C5: G***; kibuzzard-677E26C5
kibuzzard-677E26CB: G***; kibuzzard-677E26CB
kibuzzard-677E26D4: G***; kibuzzard-677E26D4
kibuzzard-677E26ED: G***; kibuzzard-677E26ED
kibuzzard-677E335B: G***; kibuzzard-677E335B
kibuzzard-677E336E: G***; kibuzzard-677E336E
kibuzzard-677E3331: G***; kibuzzard-677E3331
kibuzzard-677E3355: G***; kibuzzard-677E3355
kibuzzard-677E3368: G***; kibuzzard-677E3368
kibuzzard-677FDCF4: G***; kibuzzard-677FDCF4
kibuzzard-6786FEE0: G***; kibuzzard-6786FEE0
kibuzzard-6786FEEF: G***; kibuzzard-6786FEEF
kibuzzard-67822EAD: G***; kibuzzard-67822EAD
kibuzzard-67822EC1: G***; kibuzzard-67822EC1
kibuzzard-678236F4: G***; kibuzzard-678236F4
kibuzzard-678238A8: G***; kibuzzard-678238A8
kibuzzard-678249D1: G***; kibuzzard-678249D1
kibuzzard-678249DC: G***; kibuzzard-678249DC
kibuzzard-678771B8: G***; kibuzzard-678771B8
kibuzzard-67823702: G***; kibuzzard-67823702
kibuzzard-67823719: G***; kibuzzard-67823719
kibuzzard-67878439: G***; kibuzzard-67878439

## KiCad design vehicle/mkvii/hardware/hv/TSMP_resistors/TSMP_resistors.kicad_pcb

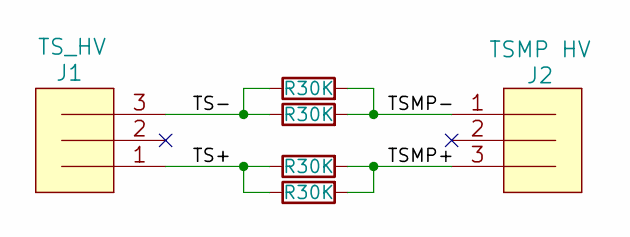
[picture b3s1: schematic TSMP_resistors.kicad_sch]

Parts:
J1: TS_HV; Connector_MicroFit_VT_3x1; MPN 436500327
J2: TSMP HV; Connector_MicroFit_VT_3x1; MPN 436500327
R1, R2, R3, R4: R30K; R_TSMP_SMD_5329

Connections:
/TS+: J1.1, R1.1, R2.1
/TS-: J1.3, R3.1, R4.1
/TSMP+: J2.3, R1.2, R2.2
/TSMP-: J2.1, R3.2, R4.2

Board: 2 copper layers, 17 parts (3 on the bottom side), 4 nets, no tracks yet.

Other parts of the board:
kibuzzard-678424C4: G***; kibuzzard-678424C4
kibuzzard-678425B2: G***; kibuzzard-678425B2
kibuzzard-6784247E: G***; kibuzzard-6784247E
kibuzzard-67842498: G***; kibuzzard-67842498
kibuzzard-67842540: G***; kibuzzard-67842540
kibuzzard-67842549: G***; kibuzzard-67842549
kibuzzard-67842553: G***; kibuzzard-67842553
kibuzzard-67842559: G***; kibuzzard-67842559
kibuzzard-67842603, kibuzzard-67842603#2: G***; kibuzzard-67842603
kibuzzard-67842782: G***; kibuzzard-67842782

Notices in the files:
parts and their libraries:
Copyright 2021 Accelerated Designs. All rights reserved.
